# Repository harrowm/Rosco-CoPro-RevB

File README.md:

# Rosco-CoPro
A 68882 floating point coprocessor board for the rosco_m68k SBC
This is a version using a ATF1502 CPLD.  It is WIP, not build, and design not finished !

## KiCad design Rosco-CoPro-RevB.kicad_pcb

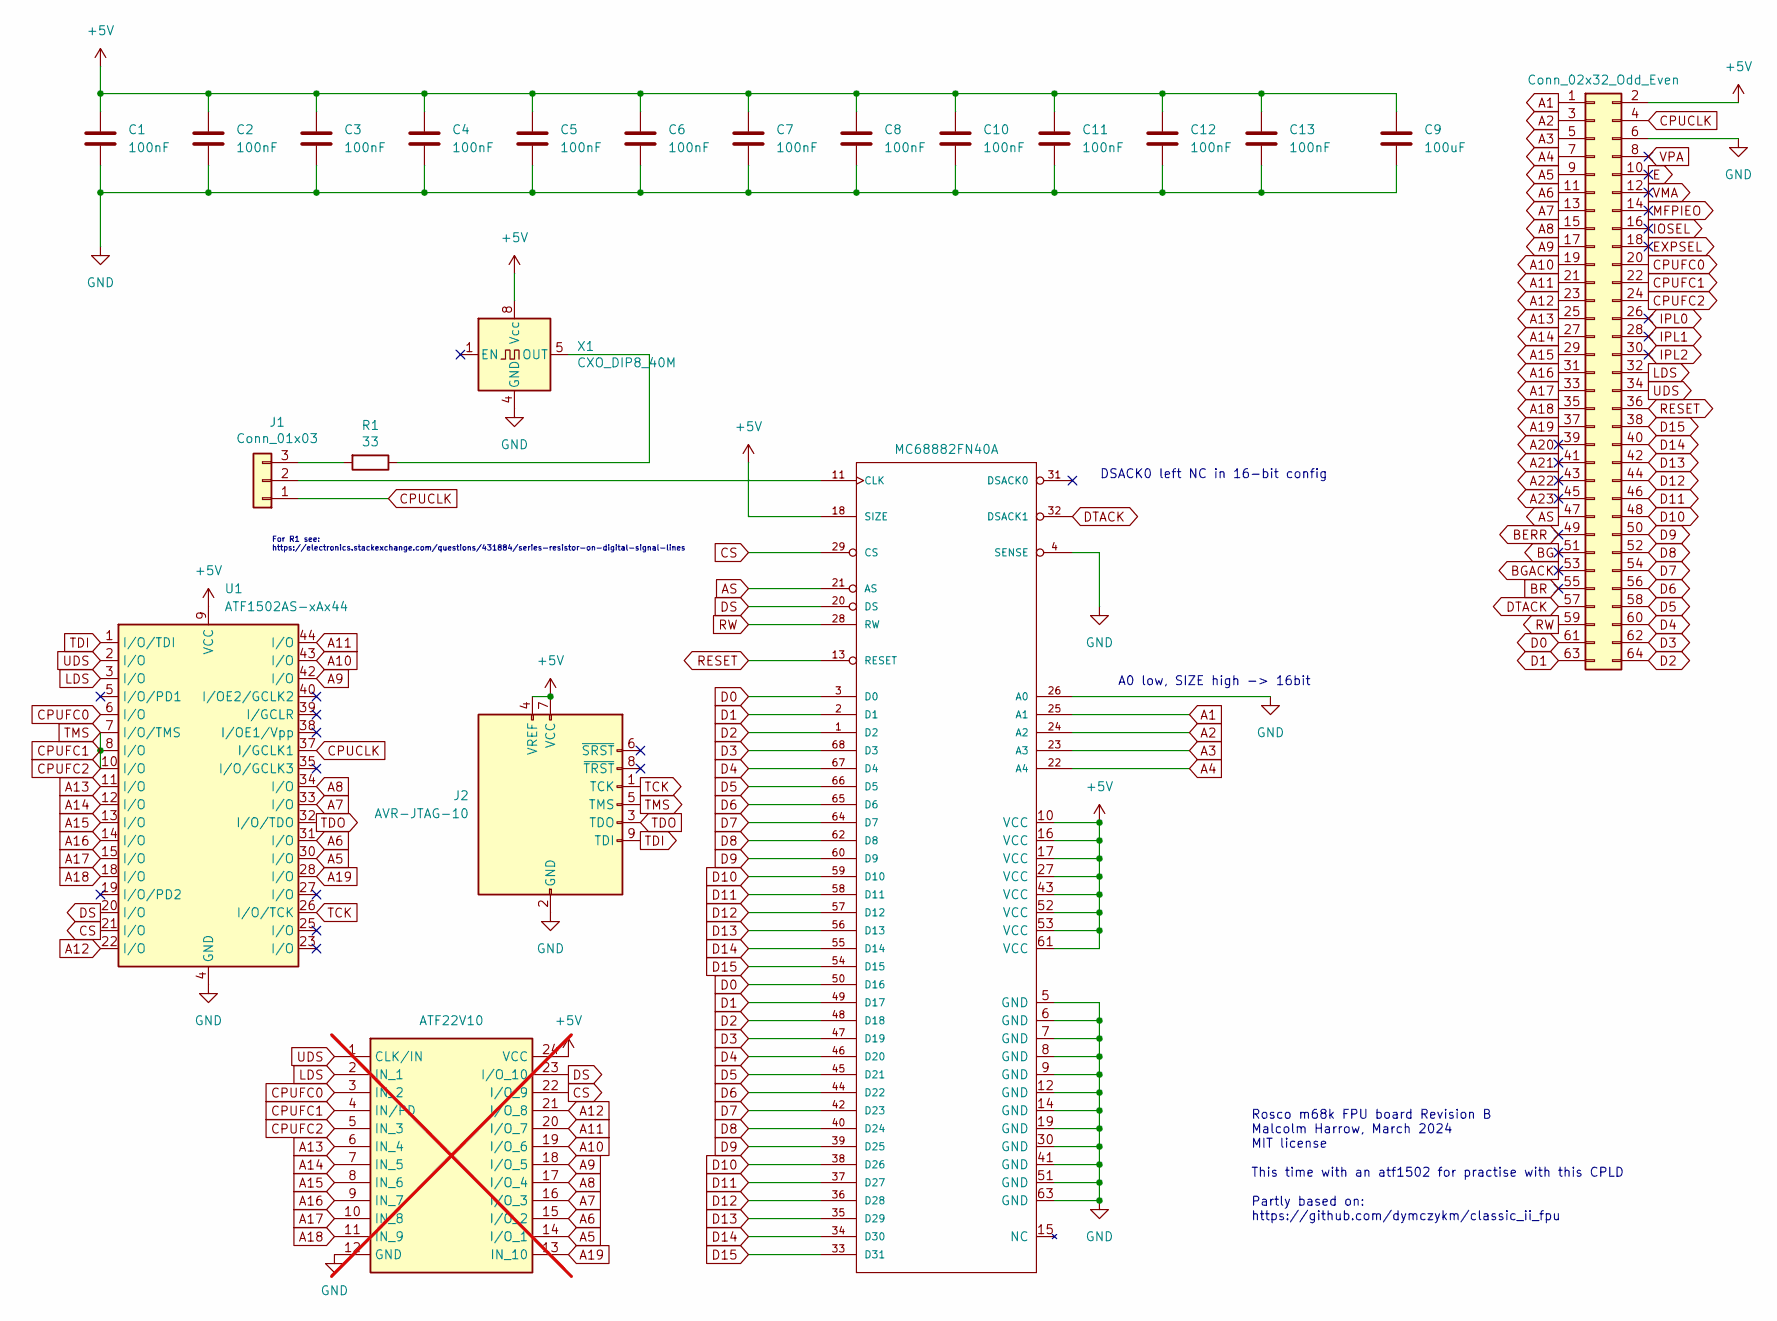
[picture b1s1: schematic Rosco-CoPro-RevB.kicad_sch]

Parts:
BUS1: Conn_02x32_Odd_Even; PinHeader_2x32_P2.54mm_Vertical
C1, C2, C3, C4, C5, C6, C7, C8, C10, C11, C12, C13: 100nF; C_Disc_D3.0mm_W2.0mm_P2.50mm
C9: 100uF; CP_Radial_D5.0mm_P2.50mm
IC1: MC68882FN40A; PLCC-68_THT-Socket
IC2: ATF22V10; DIP-24_W7.62mm_LongPads; Mouser Part Number 556-AF22V10C15PU; not fitted
J1: Conn_01x03; PinHeader_1x03_P2.54mm_Vertical
J2: AVR-JTAG-10; PinHeader_2x05_P2.54mm_Vertical
R1: 33; R_Axial_DIN0207_L6.3mm_D2.5mm_P10.16mm_Horizontal
U1: ATF1502AS-xAx44; PLCC-44_THT-Socket
X1: CXO_DIP8_40M; Oscillator_DIP-8_LargePads

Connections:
+5V: BUS1.2, C1.1, C2.1, C3.1, C4.1, C5.1, C6.1, C7.1, C8.1, C9.1, C10.1, C11.1, C12.1, C13.1, IC1.10 (VCC), IC1.16 (VCC), IC1.17 (VCC), IC1.18 (SIZE), IC1.27 (VCC), IC1.43 (VCC), IC1.52 (VCC), IC1.53 (VCC), IC1.61 (VCC), IC2.24 (VCC), J2.4 (VREF), J2.7 (VCC), U1.9 (VCC), U1.17 (VCC), U1.29 (VCC), U1.41 (VCC), X1.8 (Vcc)
A1: BUS1.1, IC1.25 (A1)
A2: BUS1.3, IC1.24 (A2)
A3: BUS1.5, IC1.23 (A3)
A4: BUS1.7, IC1.22 (A4)
A5: BUS1.9, IC2.14 (I/O_1), U1.30 (I/O)
A6: BUS1.11, IC2.15 (I/O_2), U1.31 (I/O)
A7: BUS1.13, IC2.16 (I/O_3), U1.33 (I/O)
A8: BUS1.15, IC2.17 (I/O_4), U1.34 (I/O)
A9: BUS1.17, IC2.18 (I/O_5), U1.42 (I/O)
A10: BUS1.19, IC2.19 (I/O_6), U1.43 (I/O)
A11: BUS1.21, IC2.20 (I/O_7), U1.44 (I/O)
A12: BUS1.23, IC2.21 (I/O_8), U1.22 (I/O)
A13: BUS1.25, IC2.6 (IN_4), U1.11 (I/O)
A14: BUS1.27, IC2.7 (IN_5), U1.12 (I/O)
A15: BUS1.29, IC2.8 (IN_6), U1.13 (I/O)
A16: BUS1.31, IC2.9 (IN_7), U1.14 (I/O)
A17: BUS1.33, IC2.10 (IN_8), U1.15 (I/O)
A18: BUS1.35, IC2.11 (IN_9), U1.18 (I/O)
A19: BUS1.37, IC2.13 (IN_10), U1.28 (I/O)
A20: BUS1.39
A21: BUS1.41
A22: BUS1.43
A23: BUS1.45
AS: BUS1.47, IC1.21 (AS)
BERR: BUS1.49
BG: BUS1.51
BGACK: BUS1.53
BR: BUS1.55
CPUCLK: BUS1.4, J1.1, U1.37 (I/GCLK1)
CPUFC0: BUS1.20, IC2.3 (IN_2), U1.6 (I/O)
CPUFC1: BUS1.22, BUS1.24, IC2.4 (IN/PD), IC2.5 (IN_3), J2.5 (TMS), U1.7 (I/O/TMS), U1.8 (I/O), U1.10 (I/O)
CS: IC1.29 (CS), IC2.22 (I/O_9), U1.21 (I/O)
D0: BUS1.61, IC1.3 (D0), IC1.50 (D16)
D1: BUS1.63, IC1.2 (D1), IC1.49 (D17)
D2: BUS1.64, IC1.1 (D2), IC1.48 (D18)
D3: BUS1.62, IC1.47 (D19), IC1.68 (D3)
D4: BUS1.60, IC1.46 (D20), IC1.67 (D4)
D5: BUS1.58, IC1.45 (D21), IC1.66 (D5)
D6: BUS1.56, IC1.44 (D22), IC1.65 (D6)
D7: BUS1.54, IC1.42 (D23), IC1.64 (D7)
D8: BUS1.52, IC1.40 (D24), IC1.62 (D8)
D9: BUS1.50, IC1.39 (D25), IC1.60 (D9)
D10: BUS1.48, IC1.38 (D26), IC1.59 (D10)
D11: BUS1.46, IC1.37 (D27), IC1.58 (D11)
D12: BUS1.44, IC1.36 (D28), IC1.57 (D12)
D13: BUS1.42, IC1.35 (D29), IC1.56 (D13)
D14: BUS1.40, IC1.34 (D30), IC1.55 (D14)
D15: BUS1.38, IC1.33 (D31), IC1.54 (D15)
DS: IC1.20 (DS), IC2.23 (I/O_10), U1.20 (I/O)
DTACK: BUS1.57, IC1.32 (DSACK1)
E: BUS1.10
EXPSEL: BUS1.18
GND: BUS1.6, C1.2, C2.2, C3.2, C4.2, C5.2, C6.2, C7.2, C8.2, C9.2, C10.2, C11.2, C12.2, C13.2, IC1.4 (SENSE), IC1.5 (GND), IC1.6 (GND), IC1.7 (GND), IC1.8 (GND), IC1.9 (GND), IC1.12 (GND), IC1.14 (GND), IC1.19 (GND), IC1.26 (A0), IC1.30 (GND), IC1.41 (GND), IC1.51 (GND), IC1.63 (GND), IC2.12 (GND), J2.2 (GND), J2.10 (GND), U1.4 (GND), U1.16 (GND), U1.24 (GND), U1.36 (GND), X1.4 (GND)
IOSEL: BUS1.16
IPL0: BUS1.26
IPL1: BUS1.28
IPL2: BUS1.30
LDS: BUS1.32, IC2.2 (IN_1), U1.3 (I/O)
MFPIEO: BUS1.14
unnamed: IC1.11 (CLK), J1.2
unnamed: J1.3, R1.2
unnamed: R1.1, X1.5 (OUT)
RESET: BUS1.36, IC1.13 (RESET)
RW: BUS1.59, IC1.28 (RW)
TCK: J2.1 (TCK), U1.26 (I/O/TCK)
TDI: J2.9 (TDI), U1.1 (I/O/TDI)
TDO: J2.3 (TDO), U1.32 (I/O/TDO)
UDS: BUS1.34, IC2.1 (CLK/IN), U1.2 (I/O)
VMA: BUS1.12
VPA: BUS1.8

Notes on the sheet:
Rosco m68k FPU board Revision B Malcolm Harrow, March 2024 MIT license This time with an atf1502 for practise with this CPLD Partly based on: https://github.com/dymczykm/classic_ii_fpu
A0 low, SIZE high -> 16bit
For R1 see: https://electronics.stackexchange.com/questions/431884/series-resistor-on-digital-signal-lines
DSACK0 left NC in 16-bit config

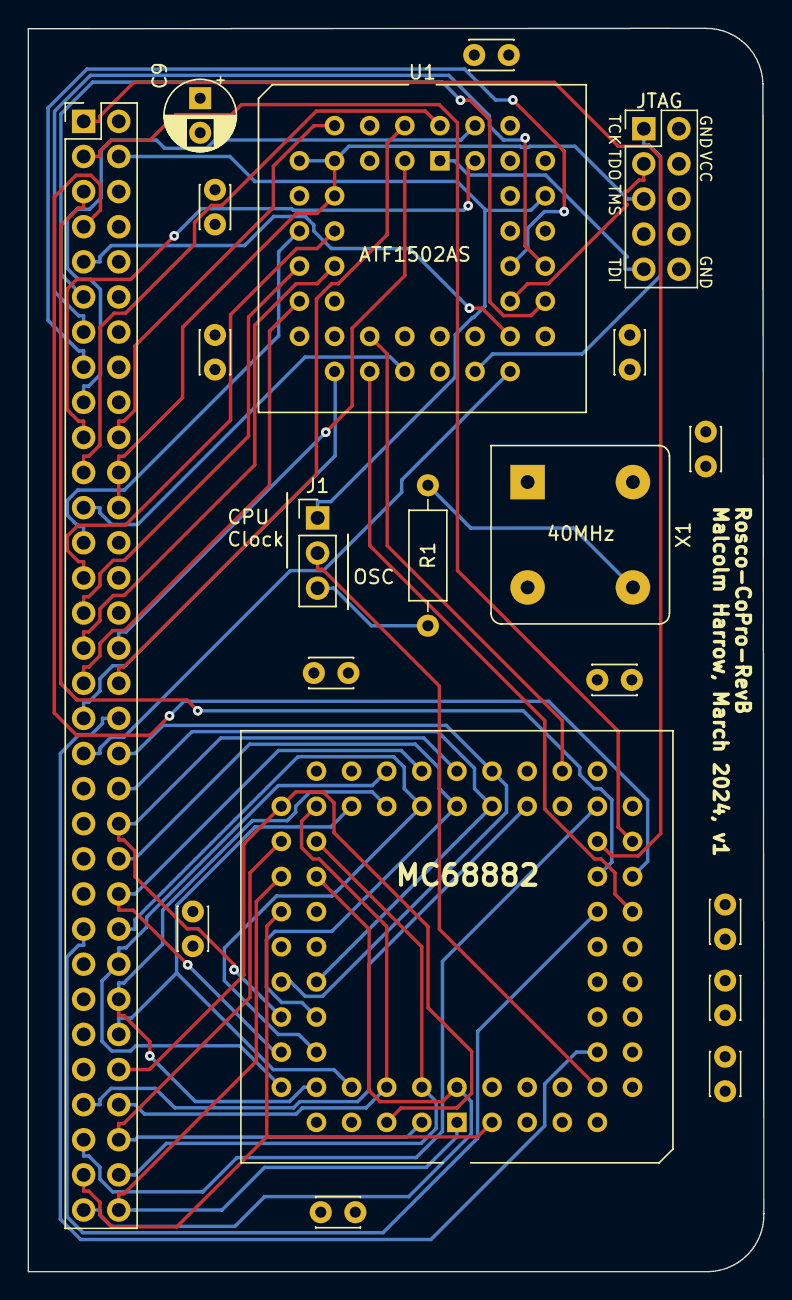
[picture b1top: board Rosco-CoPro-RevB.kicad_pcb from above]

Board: 4 copper layers, 53.2 x 89.9 mm, 20 parts (0 on the bottom side), 54 nets.

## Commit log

2025-03-13 Tidy up for mothballing
